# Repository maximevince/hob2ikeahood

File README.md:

# hob2ikeahood

## What is it?

AEG hob2hood support for Ikea Underverk Hoods

AEG hob2hood sends infrared codes from the hob in your kitchen to the hood on top of it.
E.g. AEG IKB84401FB supports this. (https://www.aeg.co.uk/kitchen/cooking/hobs/induction-hob/ikb84401fb/)

I do not have the appropriate AEG hood, that supports the hob2hood function, but rather a cheaper Ikea "Underverk"
(https://www.ikea.com/gb/en/p/underverk-built-in-extractor-hood-stainless-steel-50392326/)

## How does it work?

This project consists of a small PCB with some Arduino firmware, which will add hob2hood support to the Ikea Underverk.
It can be connected to sit in between the existing mainboard, and the buttons PCB. This way, no existing functionality is compromised.
You can still use the manual buttons, if you'd like to.

This is what the PCB looks like:

And this is what it looks like, when installed:

A bit closer:

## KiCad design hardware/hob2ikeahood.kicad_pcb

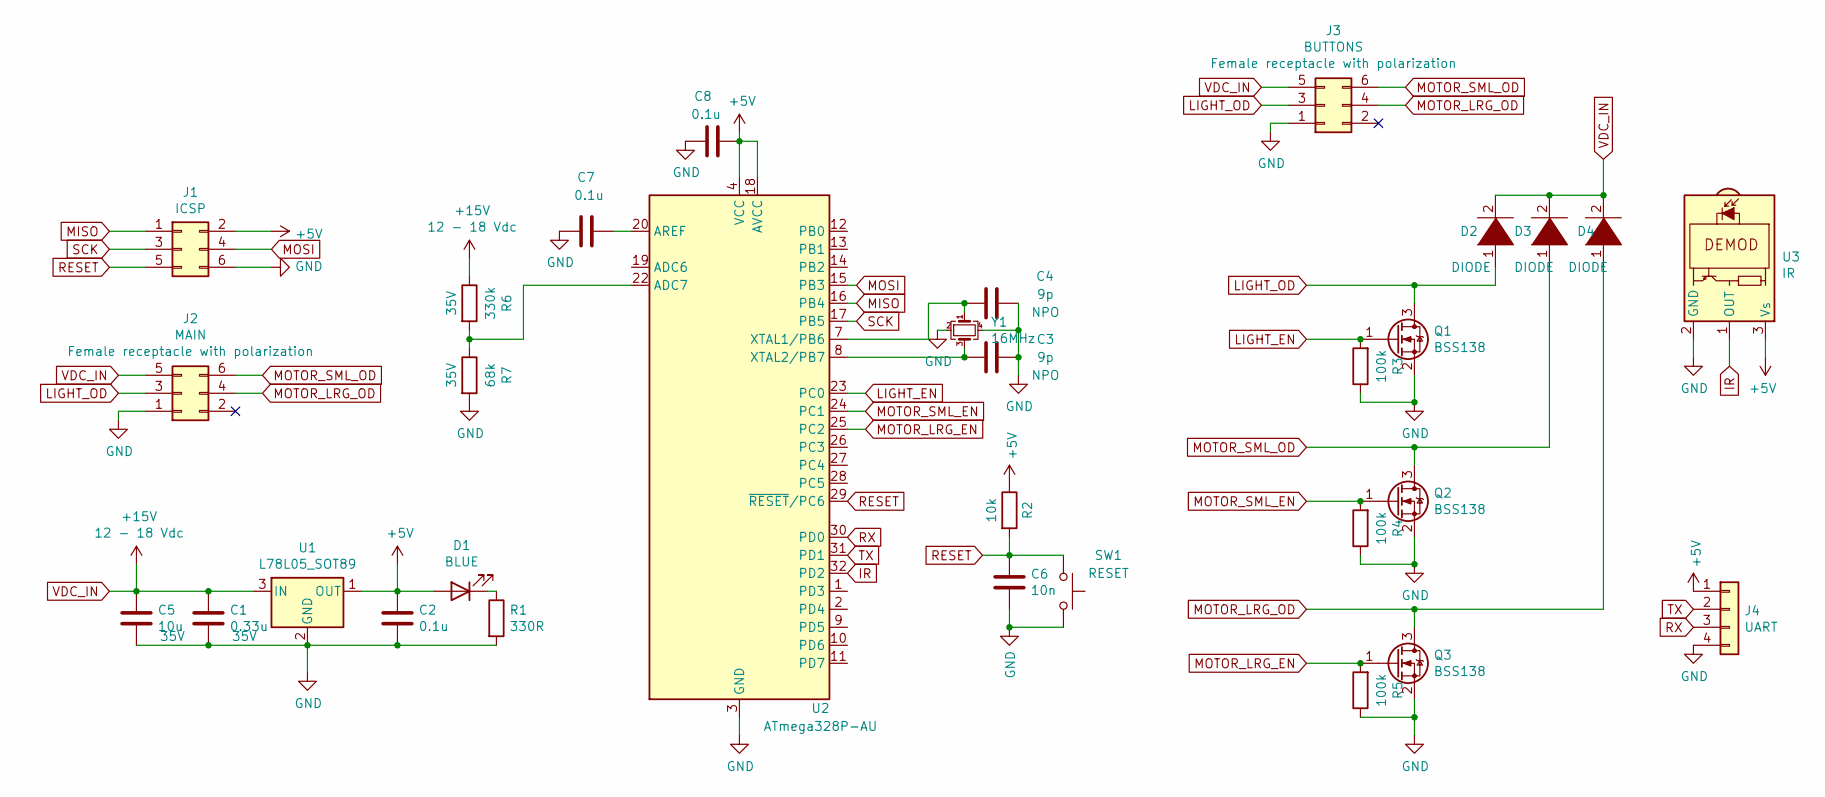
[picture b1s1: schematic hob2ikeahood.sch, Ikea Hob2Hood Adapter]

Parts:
C1: 0.33u; C_0603; Voltage rating 35V
C2, C7, C8: 0.1u; C_0603
C3, C4: 9p; C_0603
C5: 10u; C_0805; Voltage rating 35V
C6: 10n; C_0603
D1: BLUE; LED_0603
D2, D3, D4: DIODE; D_SOD-123F; Voltage rating 35V
J1: ICSP; Pin_Header_Straight_2x03_Pitch2.54mm
J2: MAIN; TE_215079-6
J3: BUTTONS; TE_215079-6
J4: UART; Pin_Header_Straight_1x04_Pitch2.54mm
Q1, Q2, Q3: BSS138; SOT-23
R1: 330R; R_0603
R2: 10k; R_0603
R3, R4, R5: 100k; R_0603
R6: 330k; R_0603; Voltage rating 35V
R7: 68k; R_0603; Voltage rating 35V
SW1: RESET; SW_SPST_B3S-1000
U1: L78L05_SOT89; SOT-89-3
U2: ATmega328P-AU; TQFP-32_7x7mm_Pitch0.8mm
U3: IR; IRReceiver_Vishay_MINICAST-3pin
Y1: 16MHz; Crystal_SMD_3225-4pin_3.2x2.5mm

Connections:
+5V: C2.1, C8.1, D1.2 (A), J1.2, J4.1, R2.1, U1.1 (OUT), U2.4 (VCC), U2.6 (VCC), U2.18 (AVCC), U3.3 (Vs)
GND: C1.2, C2.2, C3.2, C4.1, C5.2, C6.2, C7.2, C8.2, J1.6, J2.1, J3.1, J4.4, Q1.2 (S), Q2.2 (S), Q3.2 (S), R1.2, R3.1, R4.1, R5.1, R7.2, SW1.2, U1.2 (GND), U2.3 (GND), U2.5 (GND), U2.21 (GND), U3.2 (GND), Y1.2, Y1.4
IR: U2.32 (PD2), U3.1 (OUT)
LIGHT_EN: Q1.1 (G), R3.2, U2.23 (PC0)
LIGHT_OD: D2.1 (K), J2.3, J3.3, Q1.3 (D)
MISO: J1.1, U2.16 (PB4)
MOSI: J1.4, U2.15 (PB3)
MOTOR_LRG_EN: Q3.1 (G), R5.2, U2.25 (PC2)
MOTOR_LRG_OD: D4.1 (K), J2.4, J3.4, Q3.3 (D)
MOTOR_SML_EN: Q2.1 (G), R4.2, U2.24 (PC1)
MOTOR_SML_OD: D3.1 (K), J2.6, J3.6, Q2.3 (D)
unnamed: C3.1, U2.8 (XTAL2/PB7), Y1.3
unnamed: C4.2, U2.7 (XTAL1/PB6), Y1.1
unnamed: C7.1, U2.20 (AREF)
unnamed: D1.1 (K), R1.1
unnamed: R6.2, R7.1, U2.22 (ADC7)
RESET: C6.1, J1.5, R2.2, SW1.1, U2.29 (~RESET~/PC6)
RX: J4.3, U2.30 (PD0)
SCK: J1.3, U2.17 (PB5)
TX: J4.2, U2.31 (PD1)
VDC_IN: C1.1, C5.1, D2.2 (A), D3.2 (A), D4.2 (A), J2.5, J3.5, R6.1, U1.3 (IN)

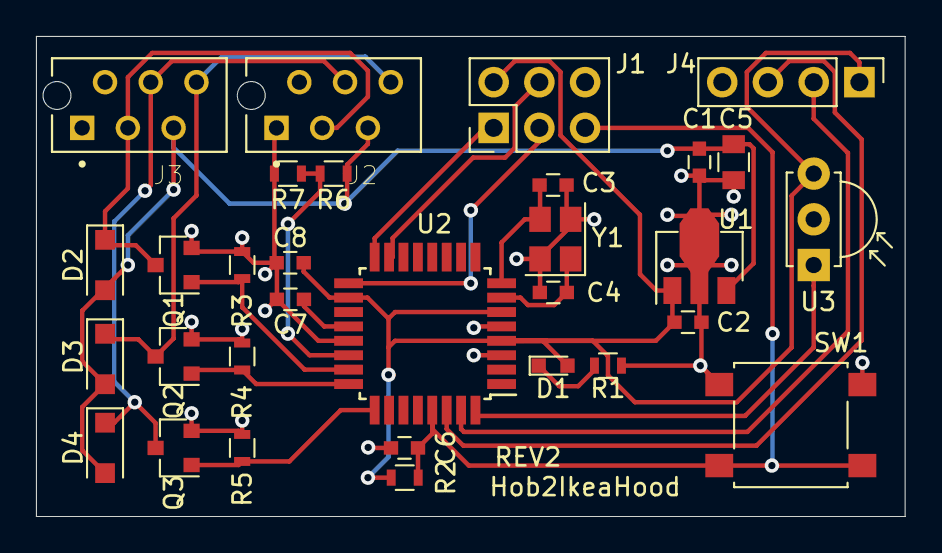
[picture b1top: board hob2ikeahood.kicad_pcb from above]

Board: 2 copper layers, 48.3 x 26.7 mm, 31 parts (0 on the bottom side), 21 nets.

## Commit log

2020-11-05 PCB Rev 2 + Arduino sketch
